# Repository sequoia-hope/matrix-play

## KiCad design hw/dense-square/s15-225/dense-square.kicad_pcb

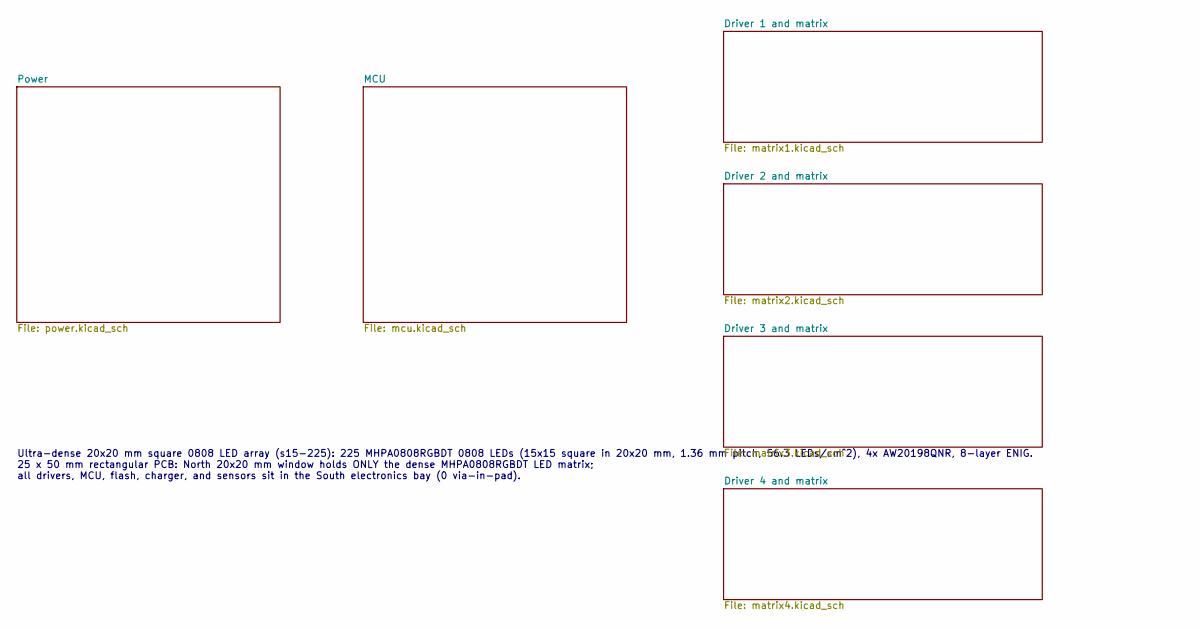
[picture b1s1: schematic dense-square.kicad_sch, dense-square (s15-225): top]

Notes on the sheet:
Ultra-dense 20x20 mm square 0808 LED array (s15-225): 225 MHPA0808RGBDT 0808 LEDs (15x15 square in 20x20 mm, 1.36 mm pitch, 56.3 LEDs/cm^2), 4x AW20198QNR, 8-layer ENIG. 25 x 50 mm rectangular PCB: North 20x20 mm window holds ONLY the dense MHPA0808RGBDT LED matrix; all drivers, MCU, flash, charger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

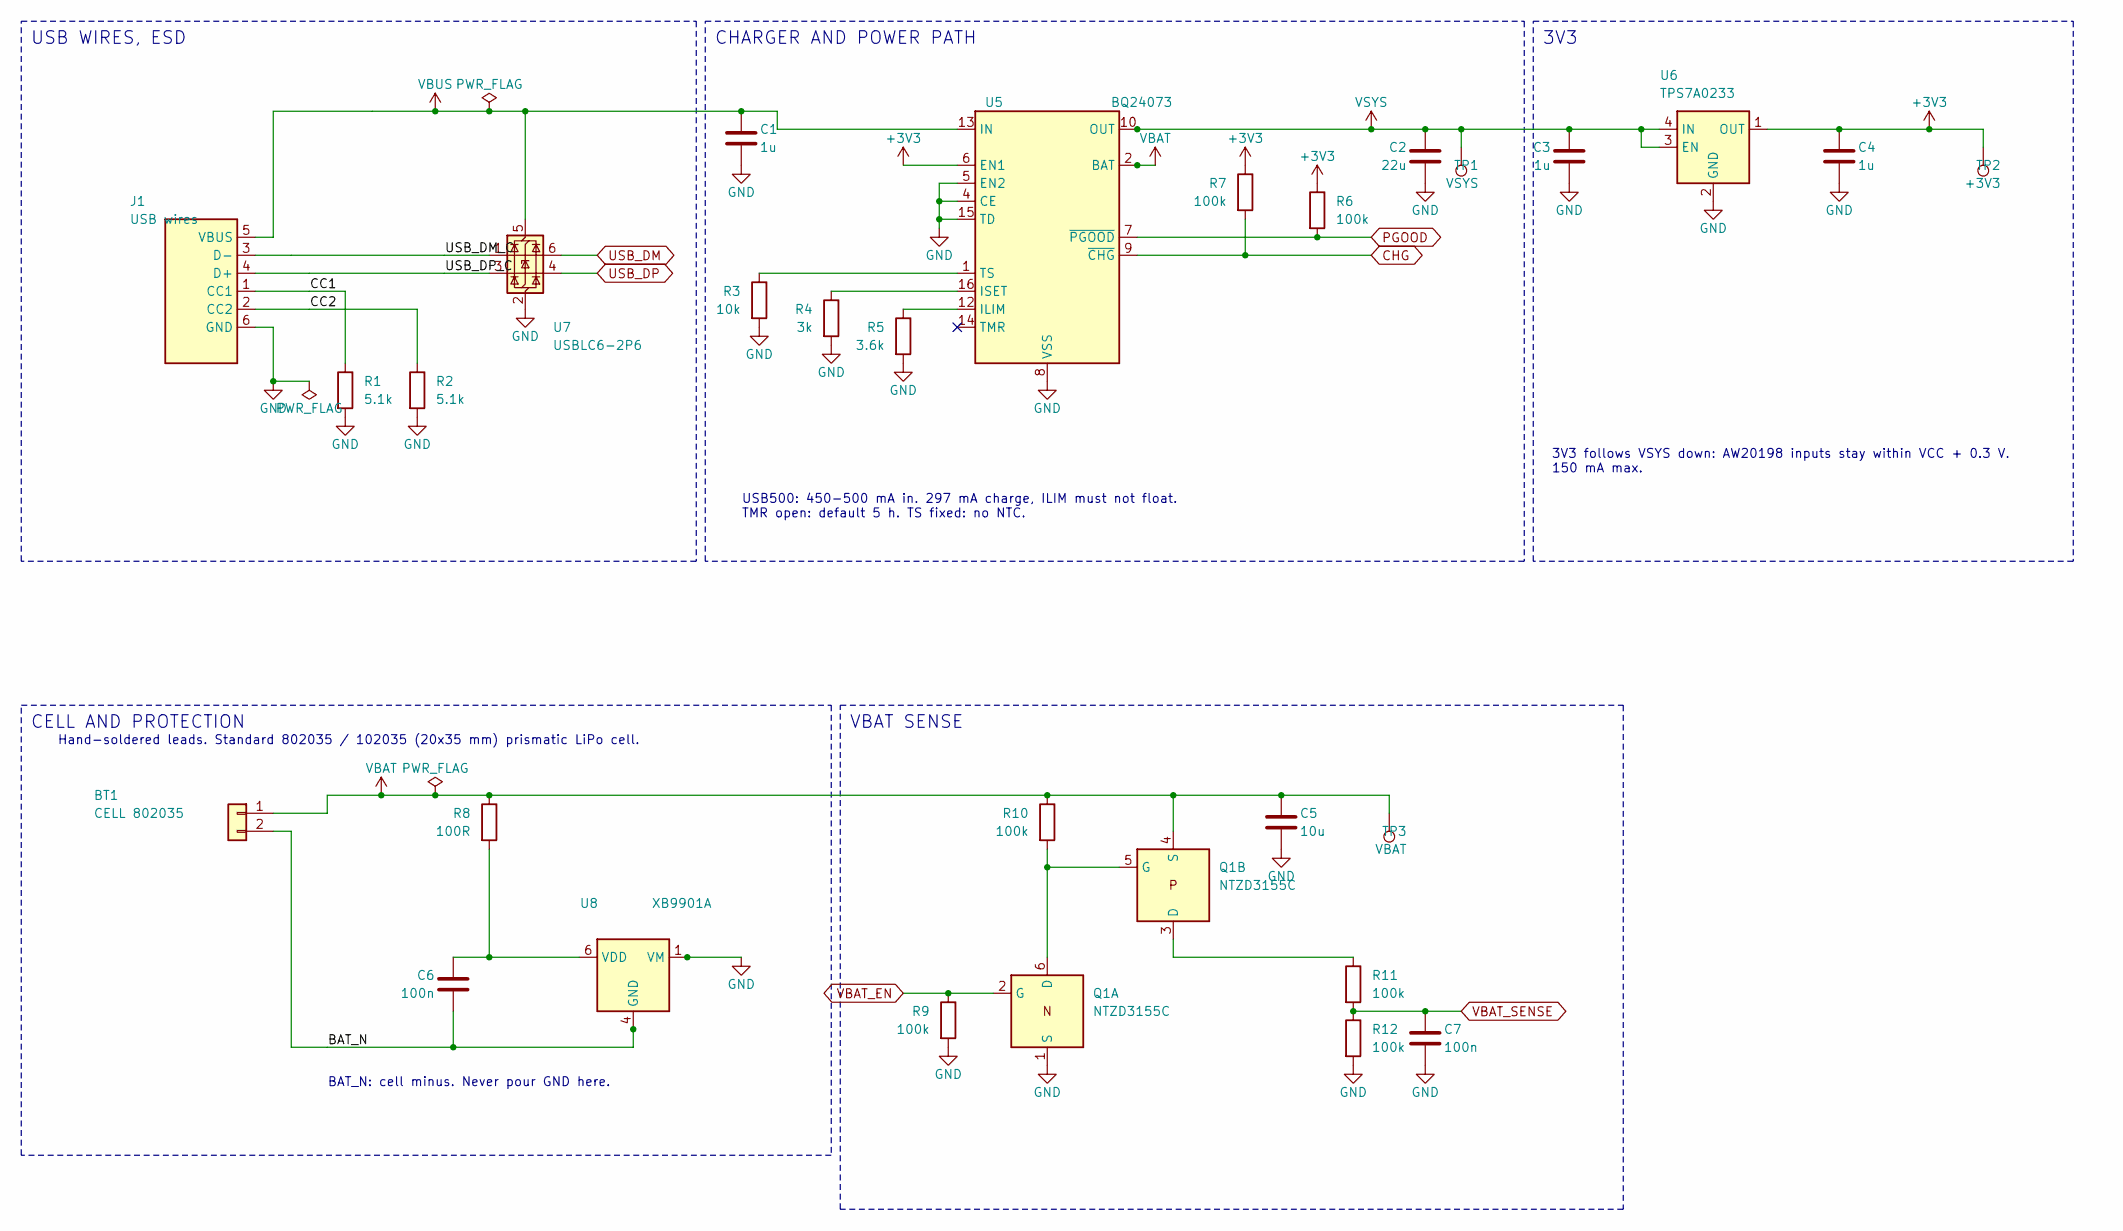
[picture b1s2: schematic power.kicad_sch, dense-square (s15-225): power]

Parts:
BT1: CELL 802035; BatteryPads; MPN 802035
C1, C3, C4: 1u; C_0402_1005Metric; MPN CL05A105KA5NQNC; LCSC C52923
C2: 22u; C_0603_1608Metric; MPN CL10A226MP8NUNE; LCSC C86295
C5: 10u; C_0603_1608Metric; MPN CL10A106KP8NNNC; LCSC C19702
C6, C7: 100n; C_0402_1005Metric; MPN CL05B104KO5NNNC; LCSC C1525
J1: USB wires; USB_Pads; MPN none, wire pads
Q1: NTZD3155C; SOT-563; MPN NTZD3155CT1G; LCSC C236117
R1, R2: 5.1k; R_0402_1005Metric; MPN 0402WGF5101TCE; LCSC C25905
R3: 10k; R_0402_1005Metric; MPN 0402WGF1002TCE; LCSC C25744
R4: 3k; R_0402_1005Metric; MPN 0402WGF3001TCE; LCSC C25784
R5: 3.6k; R_0402_1005Metric; MPN 0402WGF3601TCE; LCSC C25891
R6, R7, R9, R10, R11, R12: 100k; R_0402_1005Metric; MPN 0402WGF1003TCE; LCSC C25741
R8: 100R; R_0402_1005Metric; MPN 0402WGF1000TCE; LCSC C25076
TP1: VSYS; TestPoint_Pad_D1.0mm
TP2: +3V3; TestPoint_Pad_D1.0mm
TP3: VBAT; TestPoint_Pad_D1.0mm
U5: BQ24073; QFN-16-1EP_3x3mm_P0.5mm_EP1.7x1.7mm; MPN BQ24073RGTR; LCSC C15220
U6: TPS7A0233; Texas_X2SON-4_1x1mm_P0.65mm; MPN TPS7A0233PDQNR; LCSC C2860046
U7: USBLC6-2P6; SOT-666; MPN USBLC6-2P6; LCSC C15999
U8: XB9901A; XySemi_DFN-6_1.8x1.4mm; MPN XB9901A; LCSC C669687

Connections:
+3V3: C4.1, R6.1, R7.1, TP2.1, U5.6 (EN1), U6.1 (OUT); also elsewhere on the board
/Power/BAT_N: BT1.2, C6.2, U8.4 (GND), U8.5 (GND)
/Power/CC1: J1.1 (CC1), R1.1
/Power/CC2: J1.2 (CC2), R2.1
/Power/USB_DM_C: J1.3 (D-), U7.1 (I/O1)
/Power/USB_DP_C: J1.4 (D+), U7.3 (I/O2)
CHG: R7.2, U5.9 (~CHG); also elsewhere on the board
unnamed: Q1.5 (G), Q1.6 (D), R10.2
unnamed: Q1.3 (D), R11.1
unnamed: R5.1, U5.12 (ILIM)
unnamed: R4.1, U5.16 (ISET)
unnamed: R3.1, U5.1 (TS)
unnamed: C6.1, R8.2, U8.6 (VDD)
PGOOD: R6.2, U5.7 (~PGOOD); also elsewhere on the board
USB_DM: U7.6 (I/O1); also elsewhere on the board
USB_DP: U7.4 (I/O2); also elsewhere on the board
VBAT_EN: Q1.2 (G), R9.1; also elsewhere on the board
VBAT_SENSE: C7.1, R11.2, R12.1; also elsewhere on the board
VSYS: C2.1, C3.1, TP1.1, U5.10 (OUT), U5.11 (OUT), U6.3 (EN), U6.4 (IN); also elsewhere on the board

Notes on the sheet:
USB WIRES, ESD
USB500: 450-500 mA in. 297 mA charge, ILIM must not float. TMR open: default 5 h. TS fixed: no NTC.
CHARGER AND POWER PATH
3V3 follows VSYS down: AW20198 inputs stay within VCC + 0.3 V. 150 mA max.
3V3
Hand-soldered leads. Standard 802035 / 102035 (20x35 mm) prismatic LiPo cell.
BAT_N: cell minus. Never pour GND here.
CELL AND PROTECTION
VBAT SENSE

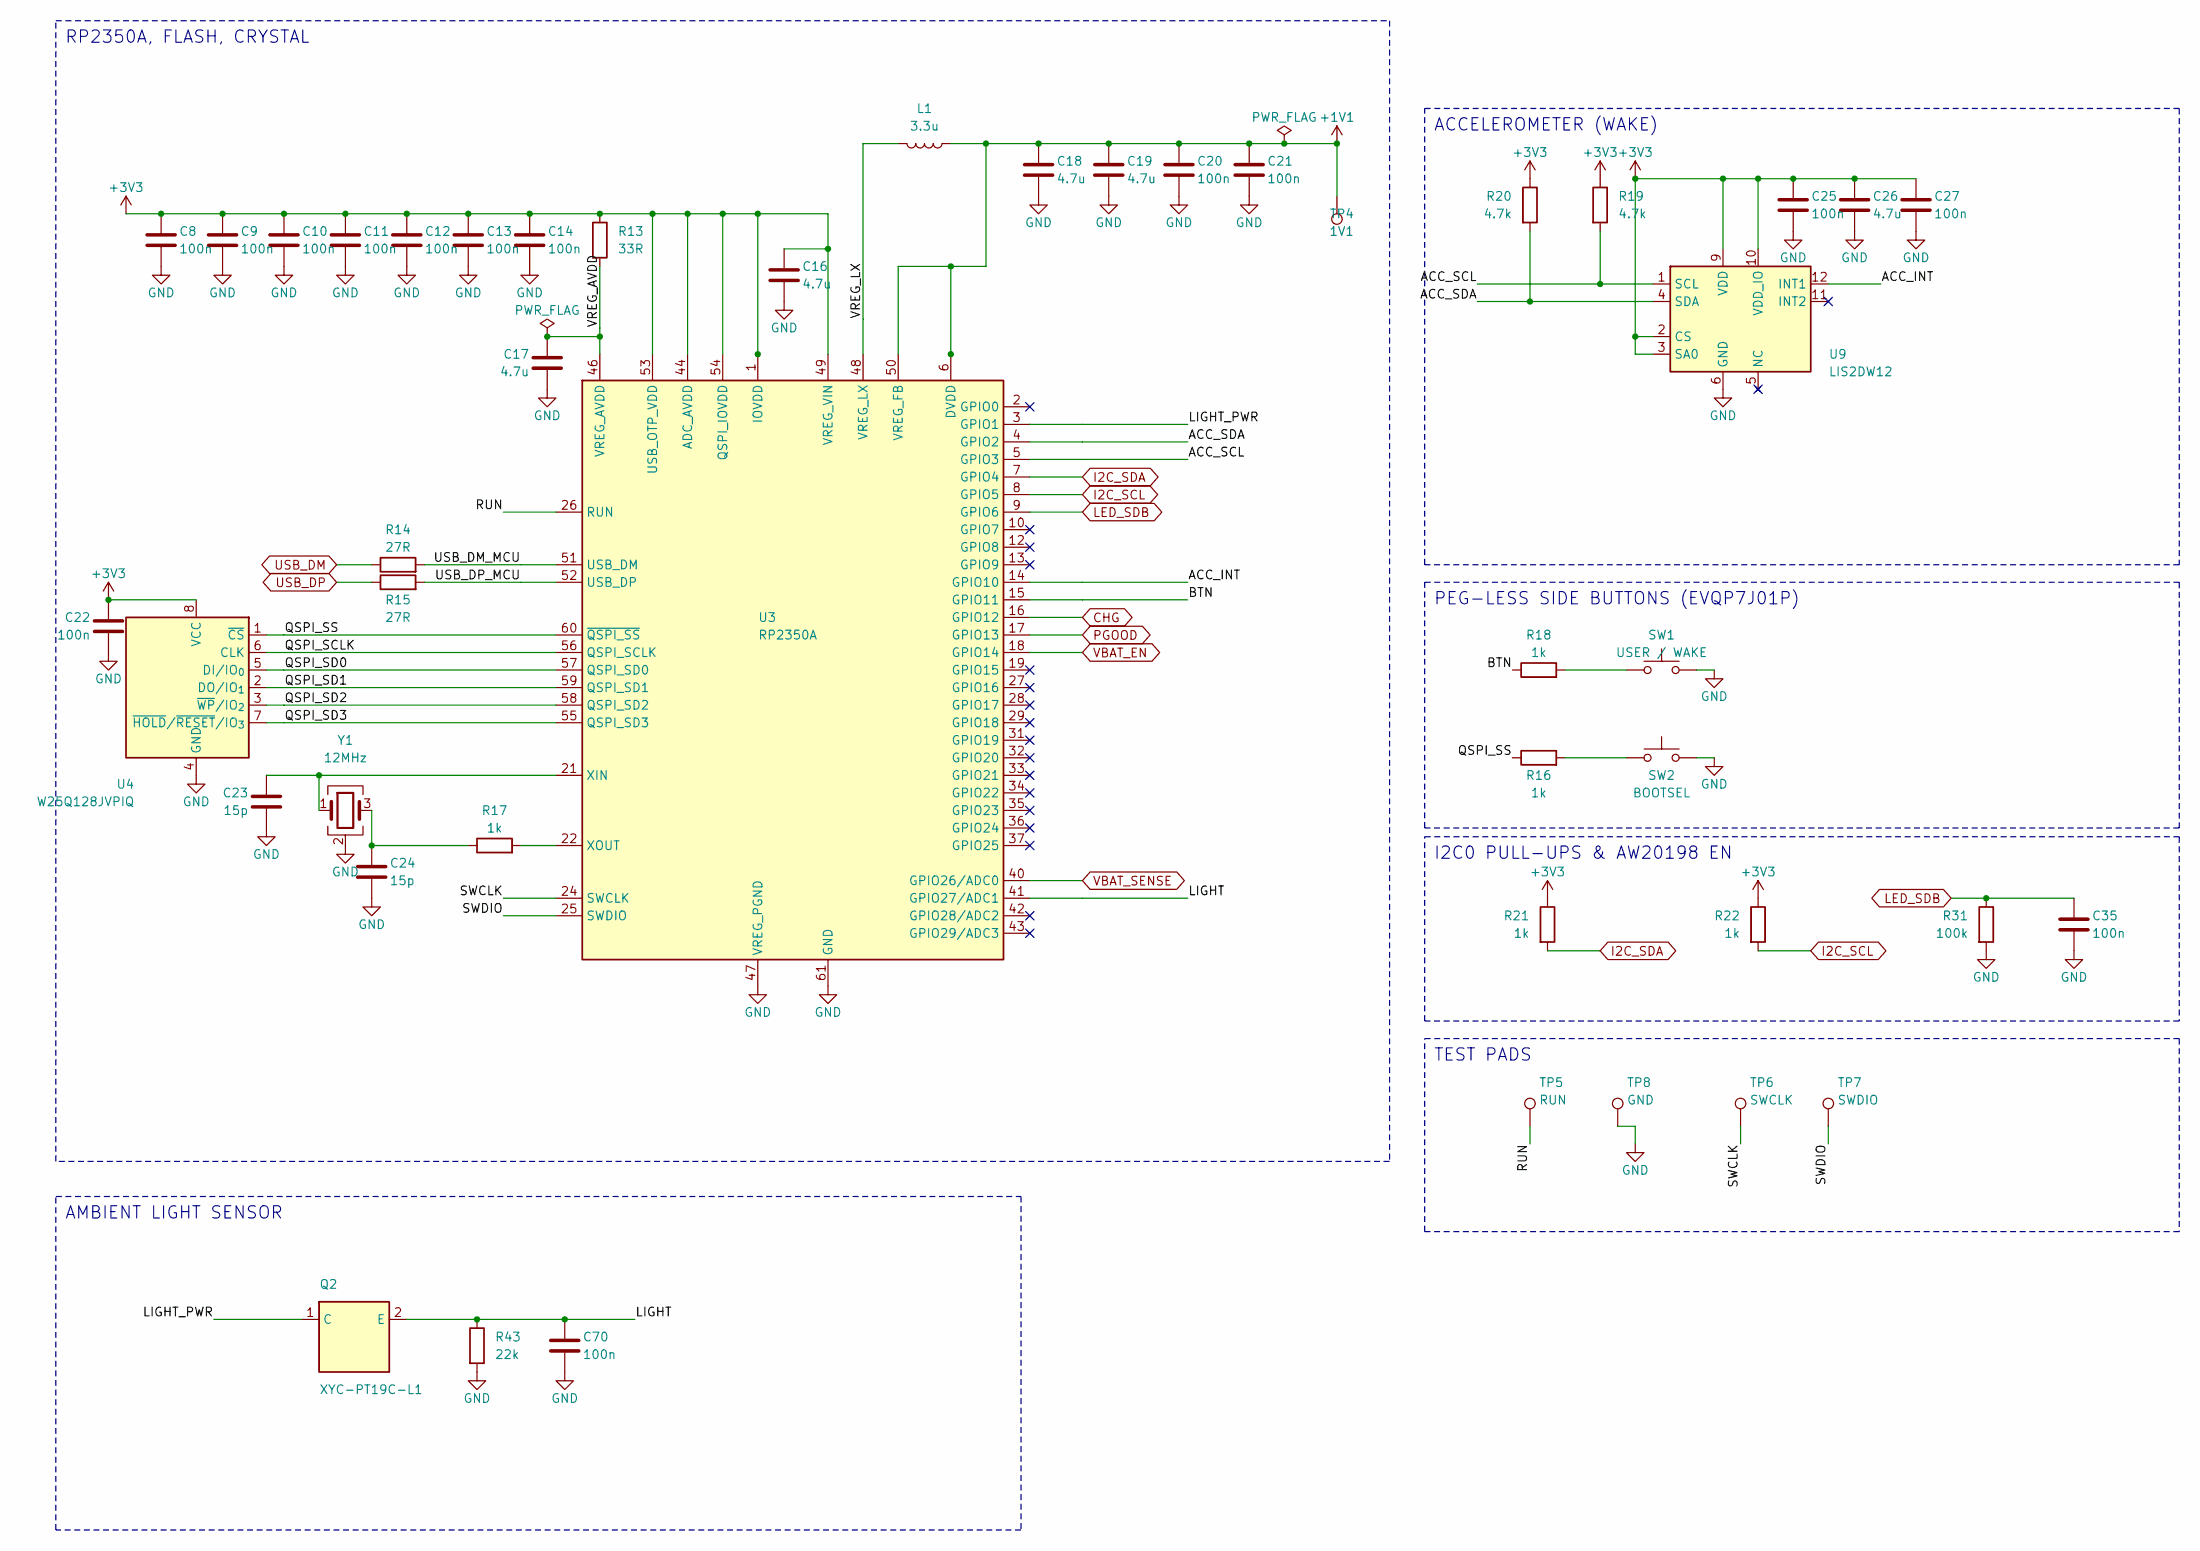
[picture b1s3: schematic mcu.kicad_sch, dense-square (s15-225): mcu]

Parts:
C8, C9, C10, C11, C12, C13, C14, C20, C21, C22, C25, C27, C35, C70: 100n; C_0402_1005Metric; MPN CL05B104KO5NNNC; LCSC C1525
C16, C18: 4.7u; C_0402_1005Metric_small_pads; MPN CL05A475MP5NRNC; LCSC C23733
C17, C19, C26: 4.7u; C_0402_1005Metric; MPN CL05A475MP5NRNC; LCSC C23733
C23, C24: 15p; C_0402_1005Metric; MPN 0402CG150J500NT; LCSC C1548
L1: 3.3u; L_pol_2016; MPN AOTA-B201610S3R3-101-T; LCSC C42411119
Q2: XYC-PT19C-L1; SENSOR_ALS-PT19; MPN XYC-PT19C-L1; LCSC C2693594
R13: 33R; R_0402_1005Metric; MPN 0402WGF330JTCE; LCSC C25105
R14, R15: 27R; R_0402_1005Metric; MPN 0402WGF270JTCE; LCSC C25100
R16, R17, R18, R21, R22: 1k; R_0402_1005Metric; MPN 0402WGF1001TCE; LCSC C11702
R19, R20: 4.7k; R_0402_1005Metric; MPN 0402WGF4701TCE; LCSC C25900
R31: 100k; R_0402_1005Metric; MPN 0402WGF1003TCE; LCSC C25741
R43: 22k; R_0402_1005Metric; MPN 0402WGF2202TCE; LCSC C25768
SW1: USER / WAKE; SW_Panasonic_EVQP7J; MPN EVQP7J01P; LCSC C2828254
SW2: BOOTSEL; SW_Panasonic_EVQP7J; MPN EVQP7J01P; LCSC C2828254
TP4: 1V1; TestPoint_Pad_D1.0mm
TP5: RUN; TestPoint_Pad_D1.0mm
TP6: SWCLK; TestPoint_Pad_D1.0mm
TP7: SWDIO; TestPoint_Pad_D1.0mm
TP8: GND; TestPoint_Pad_D1.0mm
U3: RP2350A; RP2350-QFN-60-1EP_7x7_P0.4mm_EP3.4x3.4mm_ThermalVias; MPN RP2350A; LCSC C42411118
U4: W25Q128JVPIQ; WSON-8_6x5mm_P1.27mm_NoEPCopper; MPN W25Q128JVPIQ; LCSC C190862
U9: LIS2DW12; LGA-12_2x2mm_P0.5mm; MPN LIS2DW12TR; LCSC C189624
Y1: 12MHz; Crystal_SMD_3225-4Pin_3.2x2.5mm; MPN ABM8-272-T3; LCSC C20625731

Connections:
+3V3: C8.1, C9.1, C10.1, C11.1, C12.1, C13.1, C14.1, C16.1, C22.1, C25.1, C26.1, C27.1, R13.1, R19.1, R20.1, R21.1, R22.1, U3.1 (IOVDD), U3.11 (IOVDD), U3.20 (IOVDD), U3.30 (IOVDD), U3.38 (IOVDD), U3.44 (ADC_AVDD), U3.45 (IOVDD), U3.49 (VREG_VIN), U3.53 (USB_OTP_VDD), U3.54 (QSPI_IOVDD), U4.8 (VCC), U9.2 (CS), U9.3 (SA0), U9.9 (VDD), U9.10 (VDD_IO); also elsewhere on the board
/MCU/ACC_INT: U3.14 (GPIO10), U9.12 (INT1)
/MCU/ACC_SCL: R19.2, U3.5 (GPIO3), U9.1 (SCL)
/MCU/ACC_SDA: R20.2, U3.4 (GPIO2), U9.4 (SDA)
/MCU/BTN: R18.1, U3.15 (GPIO11)
/MCU/LIGHT: C70.1, Q2.2 (E), R43.1, U3.41 (GPIO27/ADC1)
/MCU/LIGHT_PWR: Q2.1 (C), U3.3 (GPIO1)
/MCU/QSPI_SCLK: U3.56 (QSPI_SCLK), U4.6 (CLK)
/MCU/QSPI_SD0: U3.57 (QSPI_SD0), U4.5 (DI/IO_{0})
/MCU/QSPI_SD1: U3.59 (QSPI_SD1), U4.2 (DO/IO_{1})
/MCU/QSPI_SD2: U3.58 (QSPI_SD2), U4.3 (~WP/IO_{2})
/MCU/QSPI_SD3: U3.55 (QSPI_SD3), U4.7 (~HOLD/~RESET/IO_{3})
/MCU/QSPI_SS: R16.1, U3.60 (~QSPI_SS), U4.1 (~CS)
/MCU/RUN: TP5.1, U3.26 (RUN)
/MCU/SWCLK: TP6.1, U3.24 (SWCLK)
/MCU/SWDIO: TP7.1, U3.25 (SWDIO)
/MCU/USB_DM_MCU: R14.2, U3.51 (USB_DM)
/MCU/USB_DP_MCU: R15.2, U3.52 (USB_DP)
/MCU/VREG_LX: L1.2, U3.48 (VREG_LX)
CHG: U3.16 (GPIO12); also elsewhere on the board
I2C_SCL: R22.2, U3.8 (GPIO5); also elsewhere on the board
I2C_SDA: R21.2, U3.7 (GPIO4); also elsewhere on the board
LED_SDB: C35.1, R31.1, U3.9 (GPIO6); also elsewhere on the board
unnamed: C24.1, R17.1, Y1.3
unnamed: R16.2, SW2.1
unnamed: R18.2, SW1.1
unnamed: C23.1, U3.21 (XIN), Y1.1
unnamed: R17.2, U3.22 (XOUT)
PGOOD: U3.17 (GPIO13); also elsewhere on the board
USB_DM: R14.1; also elsewhere on the board
USB_DP: R15.1; also elsewhere on the board
VBAT_EN: U3.18 (GPIO14); also elsewhere on the board
VBAT_SENSE: U3.40 (GPIO26/ADC0); also elsewhere on the board

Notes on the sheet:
RP2350A, FLASH, CRYSTAL
ACCELEROMETER (WAKE)
PEG-LESS SIDE BUTTONS (EVQP7J01P)
I2C0 PULL-UPS & AW20198 EN
TEST PADS
AMBIENT LIGHT SENSOR

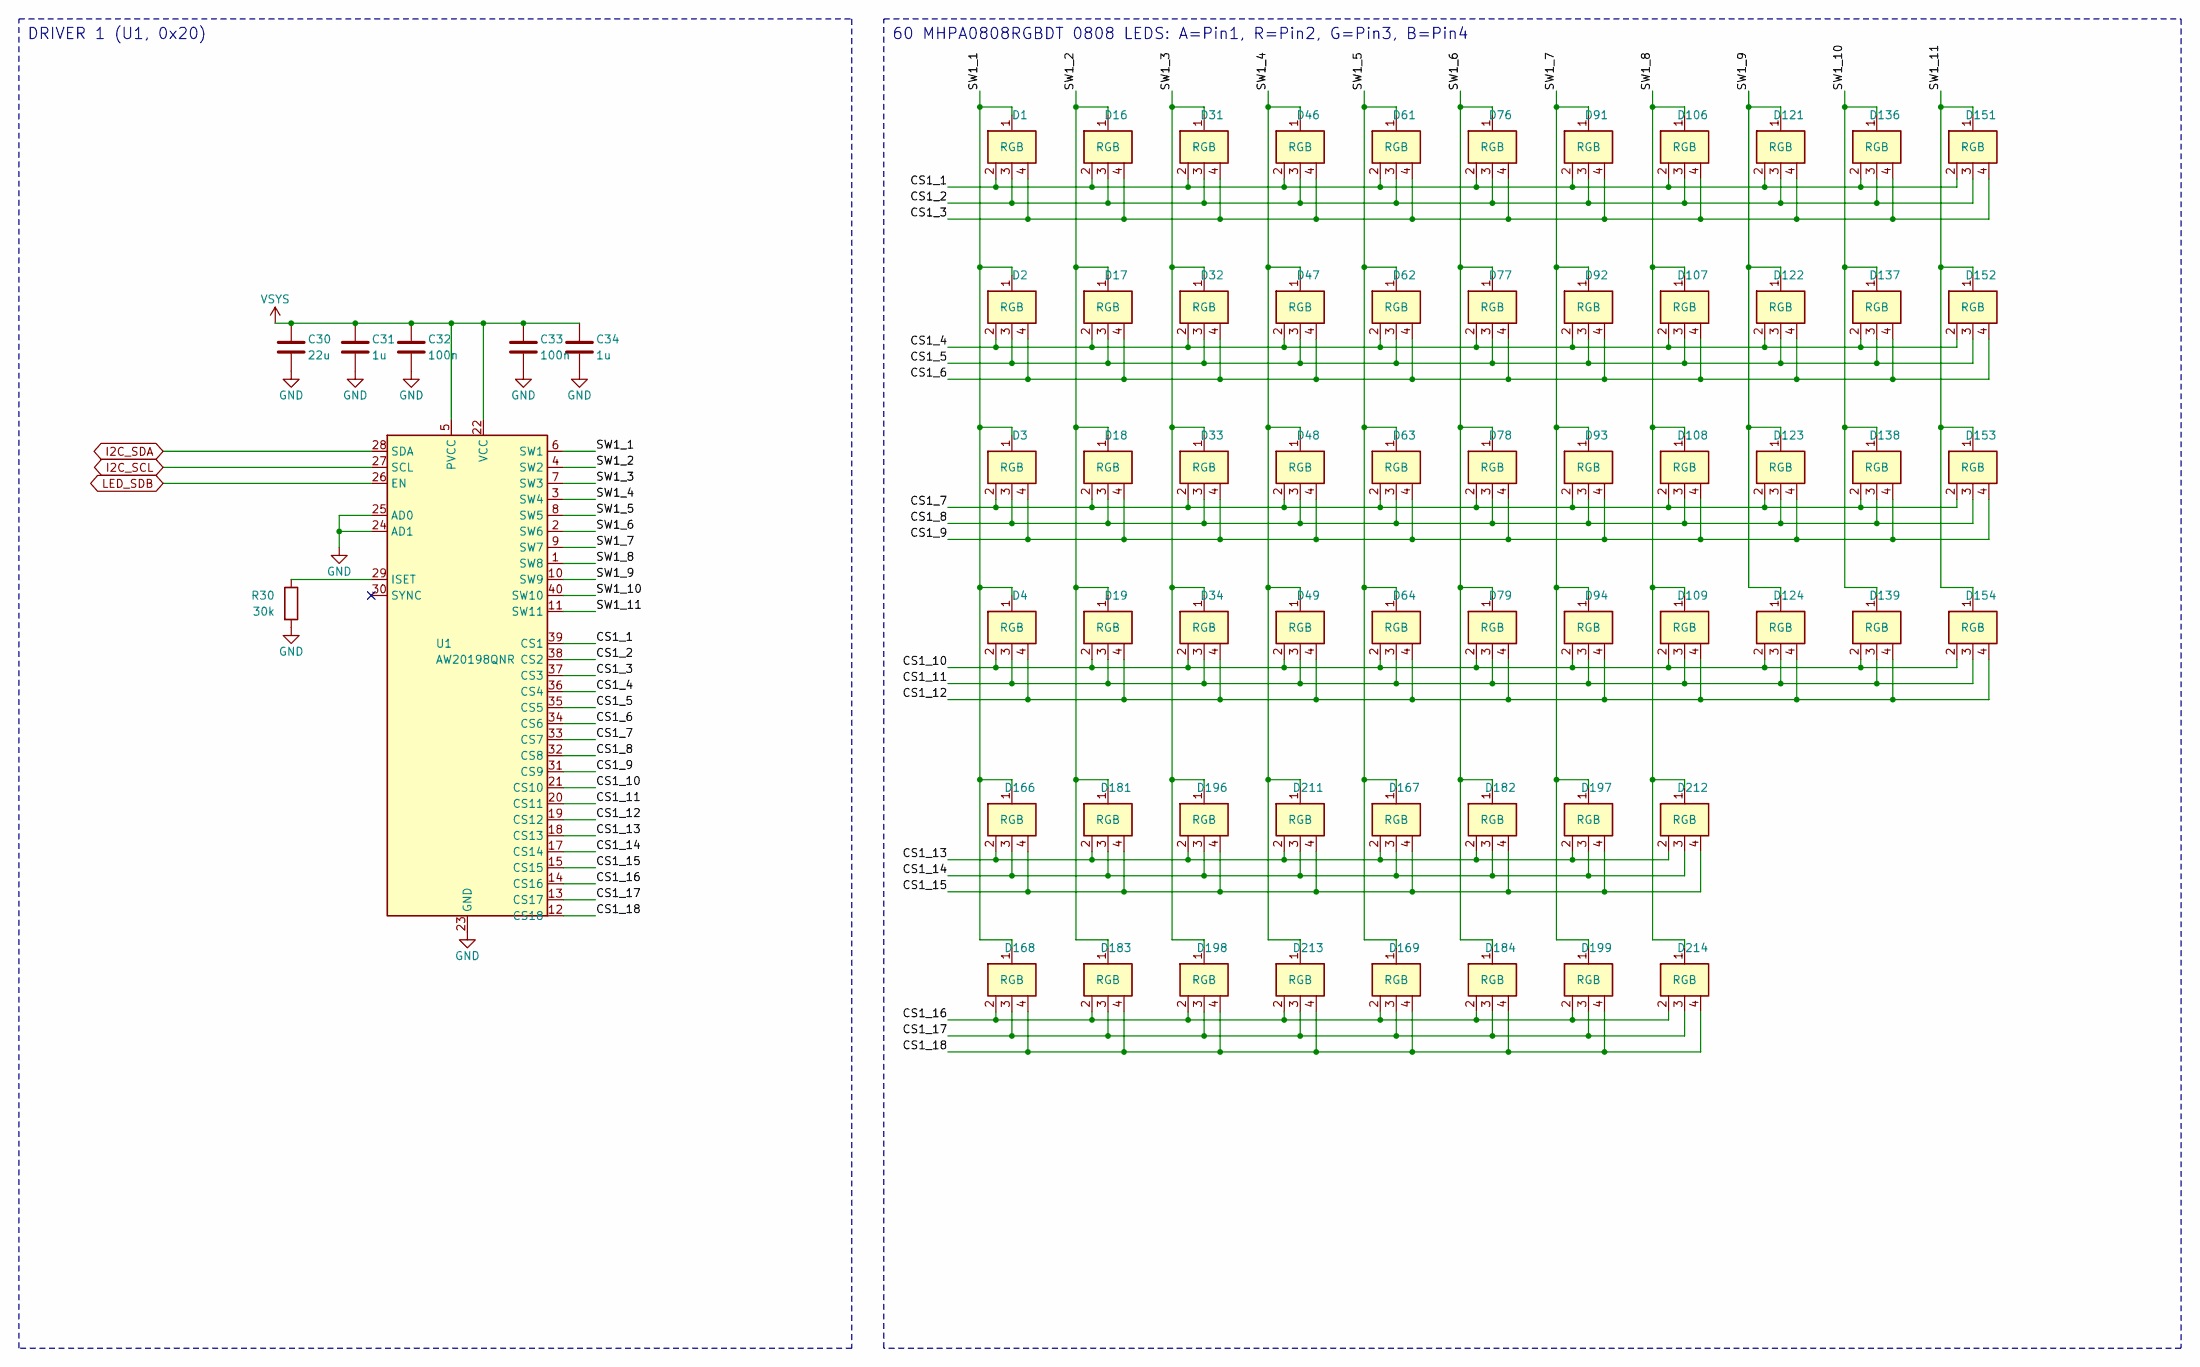
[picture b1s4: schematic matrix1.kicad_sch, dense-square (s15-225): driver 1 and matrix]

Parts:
C30: 22u; C_0603_1608Metric; MPN CL10A226MP8NUNE; LCSC C86295
C31, C34: 1u; C_0402_1005Metric; MPN CL05A105KA5NQNC; LCSC C52923
C32, C33: 100n; C_0402_1005Metric; MPN CL05B104KO5NNNC; LCSC C1525
D1, D2, D3, D4, D16, D17, D18, D19, D31, D32, D33, D34, D46, D47, D48, D49, D61, D62, D63, D64, D76, D77, D78, D79, D91, D92, D93, D94, D106, D107, D108, D109, D121, D122, D123, D124, D136, D137, D138, D139, D151, D152, D153, D154, D166, D167, D168, D169, D181, D182, D183, D184, D196, D197, D198, D199, D211, D212, D213, D214: RGB; LED_MHPA0808RGBDT; MPN MHPA0808RGBDT; LCSC C404279
R30: 30k; R_0402_1005Metric; MPN 0402WGF3002TCE; LCSC C25776
U1: AW20198QNR; AW20198_QFN-40-1EP_5x5mm_P0.4mm_EP3.4x3.4mm; MPN AW20198QNR; LCSC C5137654

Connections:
/Driver 1 and matrix/CS1_1: D1.2 (R), D16.2 (R), D31.2 (R), D46.2 (R), D61.2 (R), D76.2 (R), D91.2 (R), D106.2 (R), D121.2 (R), D136.2 (R), D151.2 (R), U1.39 (CS1)
/Driver 1 and matrix/CS1_2: D1.3 (G), D16.3 (G), D31.3 (G), D46.3 (G), D61.3 (G), D76.3 (G), D91.3 (G), D106.3 (G), D121.3 (G), D136.3 (G), D151.3 (G), U1.38 (CS2)
/Driver 1 and matrix/CS1_3: D1.4 (B), D16.4 (B), D31.4 (B), D46.4 (B), D61.4 (B), D76.4 (B), D91.4 (B), D106.4 (B), D121.4 (B), D136.4 (B), D151.4 (B), U1.37 (CS3)
/Driver 1 and matrix/CS1_4: D2.2 (R), D17.2 (R), D32.2 (R), D47.2 (R), D62.2 (R), D77.2 (R), D92.2 (R), D107.2 (R), D122.2 (R), D137.2 (R), D152.2 (R), U1.36 (CS4)
/Driver 1 and matrix/CS1_5: D2.3 (G), D17.3 (G), D32.3 (G), D47.3 (G), D62.3 (G), D77.3 (G), D92.3 (G), D107.3 (G), D122.3 (G), D137.3 (G), D152.3 (G), U1.35 (CS5)
/Driver 1 and matrix/CS1_6: D2.4 (B), D17.4 (B), D32.4 (B), D47.4 (B), D62.4 (B), D77.4 (B), D92.4 (B), D107.4 (B), D122.4 (B), D137.4 (B), D152.4 (B), U1.34 (CS6)
/Driver 1 and matrix/CS1_7: D3.2 (R), D18.2 (R), D33.2 (R), D48.2 (R), D63.2 (R), D78.2 (R), D93.2 (R), D108.2 (R), D123.2 (R), D138.2 (R), D153.2 (R), U1.33 (CS7)
/Driver 1 and matrix/CS1_8: D3.3 (G), D18.3 (G), D33.3 (G), D48.3 (G), D63.3 (G), D78.3 (G), D93.3 (G), D108.3 (G), D123.3 (G), D138.3 (G), D153.3 (G), U1.32 (CS8)
/Driver 1 and matrix/CS1_9: D3.4 (B), D18.4 (B), D33.4 (B), D48.4 (B), D63.4 (B), D78.4 (B), D93.4 (B), D108.4 (B), D123.4 (B), D138.4 (B), D153.4 (B), U1.31 (CS9)
/Driver 1 and matrix/CS1_10: D4.2 (R), D19.2 (R), D34.2 (R), D49.2 (R), D64.2 (R), D79.2 (R), D94.2 (R), D109.2 (R), D124.2 (R), D139.2 (R), D154.2 (R), U1.21 (CS10)
/Driver 1 and matrix/CS1_11: D4.3 (G), D19.3 (G), D34.3 (G), D49.3 (G), D64.3 (G), D79.3 (G), D94.3 (G), D109.3 (G), D124.3 (G), D139.3 (G), D154.3 (G), U1.20 (CS11)
/Driver 1 and matrix/CS1_12: D4.4 (B), D19.4 (B), D34.4 (B), D49.4 (B), D64.4 (B), D79.4 (B), D94.4 (B), D109.4 (B), D124.4 (B), D139.4 (B), D154.4 (B), U1.19 (CS12)
/Driver 1 and matrix/CS1_13: D166.2 (R), D167.2 (R), D181.2 (R), D182.2 (R), D196.2 (R), D197.2 (R), D211.2 (R), D212.2 (R), U1.18 (CS13)
/Driver 1 and matrix/CS1_14: D166.3 (G), D167.3 (G), D181.3 (G), D182.3 (G), D196.3 (G), D197.3 (G), D211.3 (G), D212.3 (G), U1.17 (CS14)
/Driver 1 and matrix/CS1_15: D166.4 (B), D167.4 (B), D181.4 (B), D182.4 (B), D196.4 (B), D197.4 (B), D211.4 (B), D212.4 (B), U1.15 (CS15)
/Driver 1 and matrix/CS1_16: D168.2 (R), D169.2 (R), D183.2 (R), D184.2 (R), D198.2 (R), D199.2 (R), D213.2 (R), D214.2 (R), U1.14 (CS16)
/Driver 1 and matrix/CS1_17: D168.3 (G), D169.3 (G), D183.3 (G), D184.3 (G), D198.3 (G), D199.3 (G), D213.3 (G), D214.3 (G), U1.13 (CS17)
/Driver 1 and matrix/CS1_18: D168.4 (B), D169.4 (B), D183.4 (B), D184.4 (B), D198.4 (B), D199.4 (B), D213.4 (B), D214.4 (B), U1.12 (CS18)
/Driver 1 and matrix/SW1_1: D1.1 (A), D2.1 (A), D3.1 (A), D4.1 (A), D166.1 (A), D168.1 (A), U1.6 (SW1)
/Driver 1 and matrix/SW1_2: D16.1 (A), D17.1 (A), D18.1 (A), D19.1 (A), D181.1 (A), D183.1 (A), U1.4 (SW2)
/Driver 1 and matrix/SW1_3: D31.1 (A), D32.1 (A), D33.1 (A), D34.1 (A), D196.1 (A), D198.1 (A), U1.7 (SW3)
/Driver 1 and matrix/SW1_4: D46.1 (A), D47.1 (A), D48.1 (A), D49.1 (A), D211.1 (A), D213.1 (A), U1.3 (SW4)
/Driver 1 and matrix/SW1_5: D61.1 (A), D62.1 (A), D63.1 (A), D64.1 (A), D167.1 (A), D169.1 (A), U1.8 (SW5)
/Driver 1 and matrix/SW1_6: D76.1 (A), D77.1 (A), D78.1 (A), D79.1 (A), D182.1 (A), D184.1 (A), U1.2 (SW6)
/Driver 1 and matrix/SW1_7: D91.1 (A), D92.1 (A), D93.1 (A), D94.1 (A), D197.1 (A), D199.1 (A), U1.9 (SW7)
/Driver 1 and matrix/SW1_8: D106.1 (A), D107.1 (A), D108.1 (A), D109.1 (A), D212.1 (A), D214.1 (A), U1.1 (SW8)
/Driver 1 and matrix/SW1_9: D121.1 (A), D122.1 (A), D123.1 (A), D124.1 (A), U1.10 (SW9)
/Driver 1 and matrix/SW1_10: D136.1 (A), D137.1 (A), D138.1 (A), D139.1 (A), U1.40 (SW10)
/Driver 1 and matrix/SW1_11: D151.1 (A), D152.1 (A), D153.1 (A), D154.1 (A), U1.11 (SW11)
I2C_SCL: U1.27 (SCL); also elsewhere on the board
I2C_SDA: U1.28 (SDA); also elsewhere on the board
LED_SDB: U1.26 (EN); also elsewhere on the board
unnamed: R30.1, U1.29 (ISET)
VSYS: C30.1, C31.1, C32.1, C33.1, C34.1, U1.5 (PVCC), U1.22 (VCC); also elsewhere on the board

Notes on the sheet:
DRIVER 1 (U1, 0x20)
60 MHPA0808RGBDT 0808 LEDS: A=Pin1, R=Pin2, G=Pin3, B=Pin4

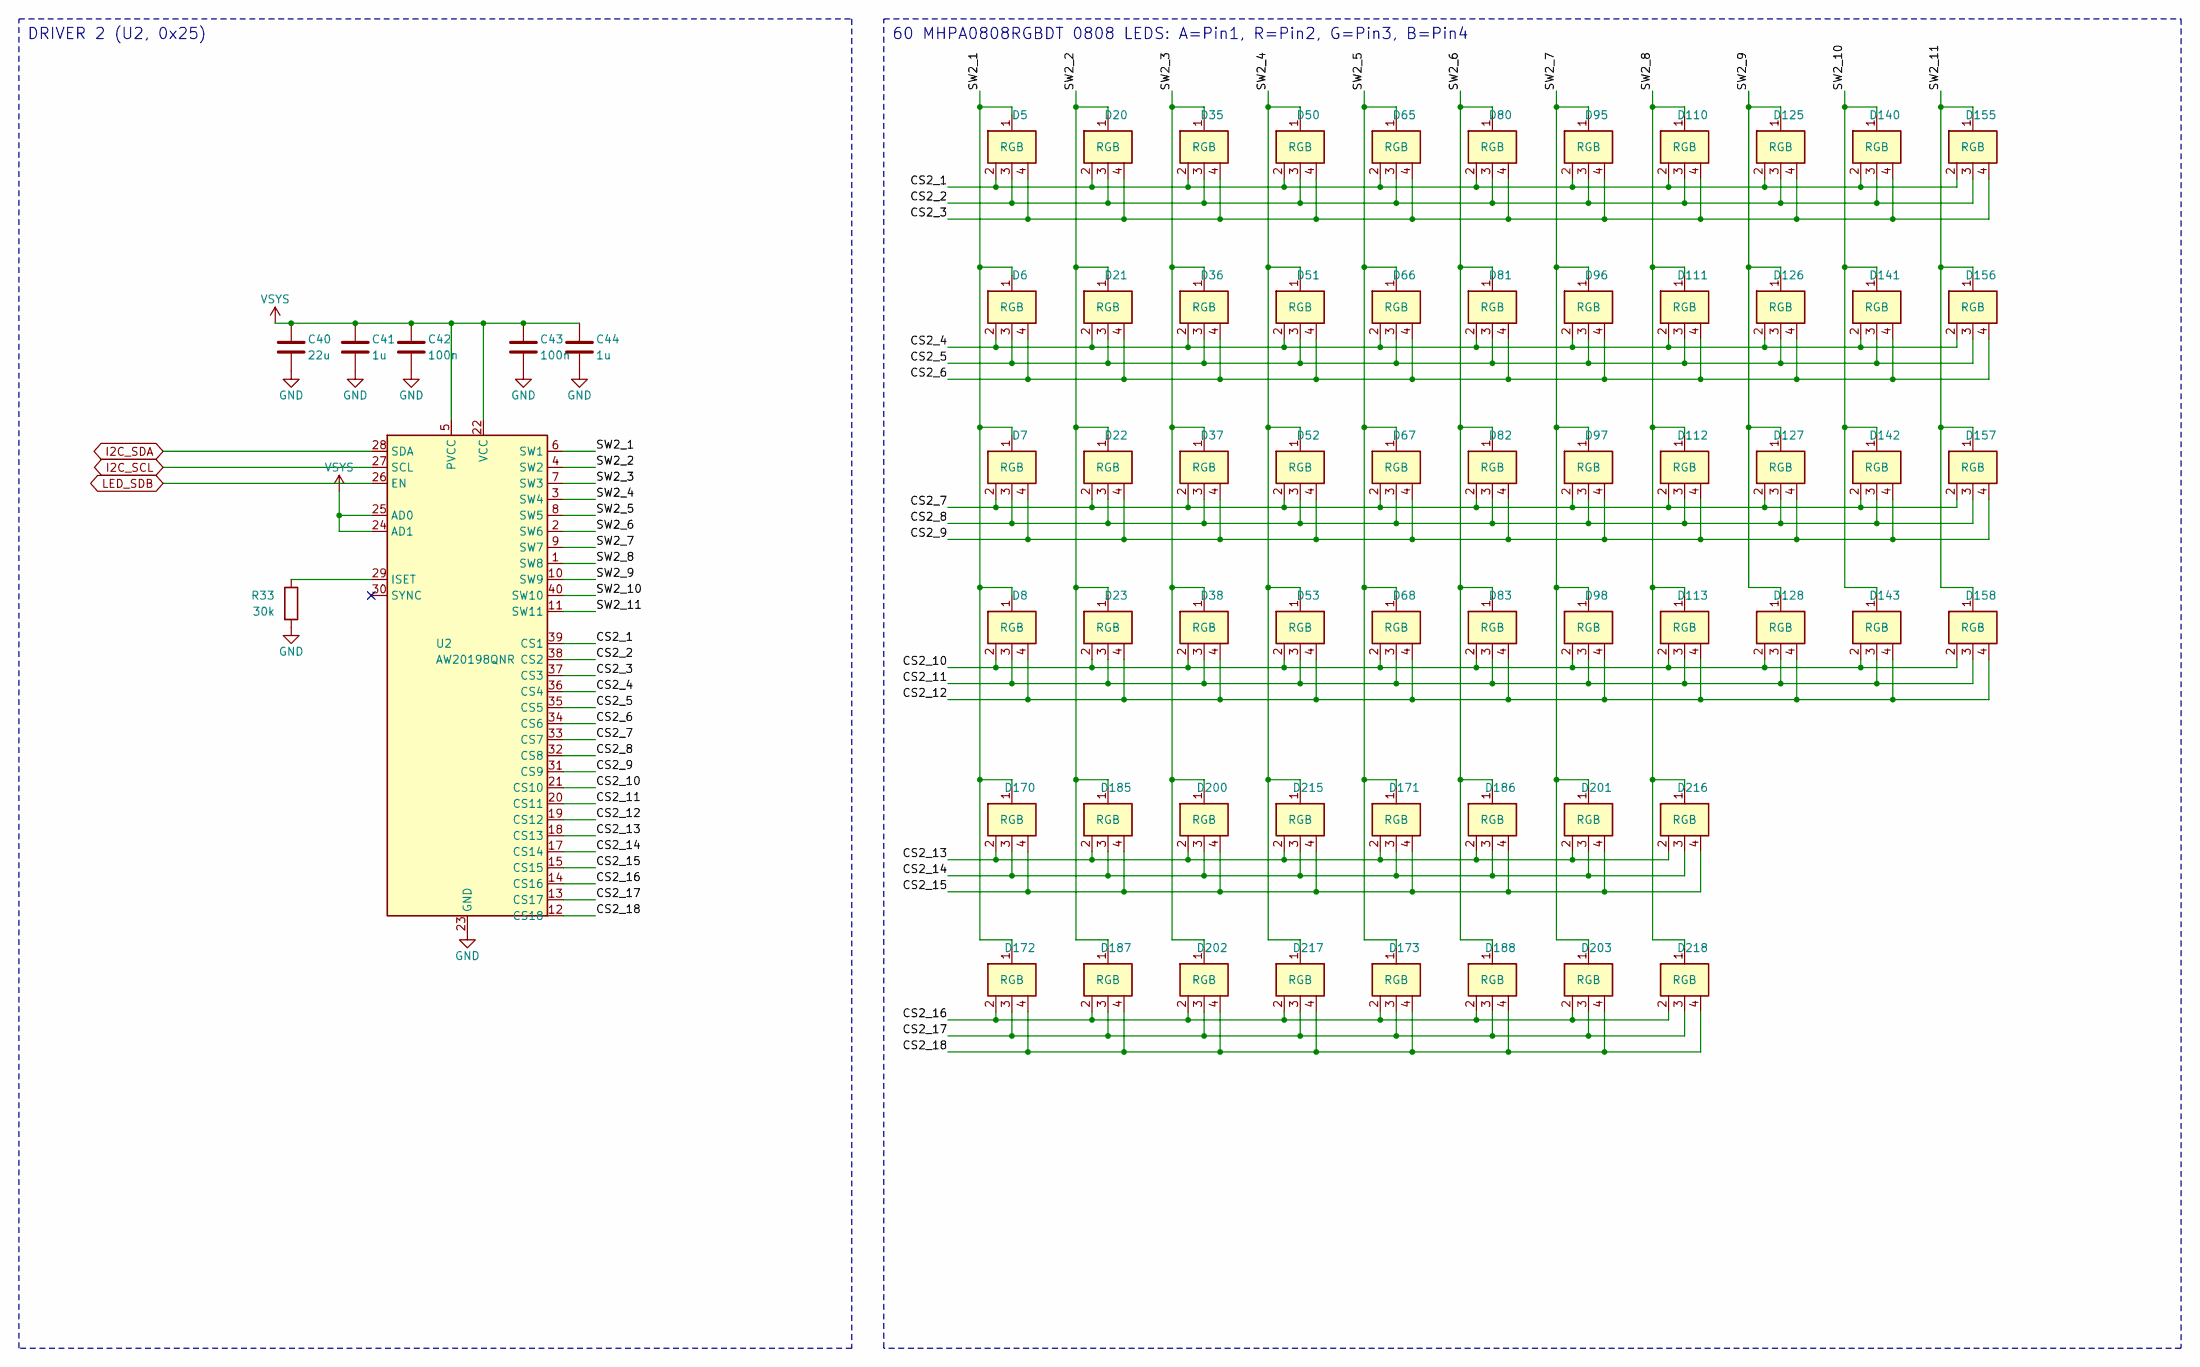
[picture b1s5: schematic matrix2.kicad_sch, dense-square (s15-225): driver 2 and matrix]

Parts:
C40: 22u; C_0603_1608Metric; MPN CL10A226MP8NUNE; LCSC C86295
C41, C44: 1u; C_0402_1005Metric; MPN CL05A105KA5NQNC; LCSC C52923
C42, C43: 100n; C_0402_1005Metric; MPN CL05B104KO5NNNC; LCSC C1525
D5, D6, D7, D8, D20, D21, D22, D23, D35, D36, D37, D38, D50, D51, D52, D53, D65, D66, D67, D68, D80, D81, D82, D83, D95, D96, D97, D98, D110, D111, D112, D113, D125, D126, D127, D128, D140, D141, D142, D143, D155, D156, D157, D158, D170, D171, D172, D173, D185, D186, D187, D188, D200, D201, D202, D203, D215, D216, D217, D218: RGB; LED_MHPA0808RGBDT; MPN MHPA0808RGBDT; LCSC C404279
R33: 30k; R_0402_1005Metric; MPN 0402WGF3002TCE; LCSC C25776
U2: AW20198QNR; AW20198_QFN-40-1EP_5x5mm_P0.4mm_EP3.4x3.4mm; MPN AW20198QNR; LCSC C5137654

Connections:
/Driver 2 and matrix/CS2_1: D5.2 (R), D20.2 (R), D35.2 (R), D50.2 (R), D65.2 (R), D80.2 (R), D95.2 (R), D110.2 (R), D125.2 (R), D140.2 (R), D155.2 (R), U2.39 (CS1)
/Driver 2 and matrix/CS2_2: D5.3 (G), D20.3 (G), D35.3 (G), D50.3 (G), D65.3 (G), D80.3 (G), D95.3 (G), D110.3 (G), D125.3 (G), D140.3 (G), D155.3 (G), U2.38 (CS2)
/Driver 2 and matrix/CS2_3: D5.4 (B), D20.4 (B), D35.4 (B), D50.4 (B), D65.4 (B), D80.4 (B), D95.4 (B), D110.4 (B), D125.4 (B), D140.4 (B), D155.4 (B), U2.37 (CS3)
/Driver 2 and matrix/CS2_4: D6.2 (R), D21.2 (R), D36.2 (R), D51.2 (R), D66.2 (R), D81.2 (R), D96.2 (R), D111.2 (R), D126.2 (R), D141.2 (R), D156.2 (R), U2.36 (CS4)
/Driver 2 and matrix/CS2_5: D6.3 (G), D21.3 (G), D36.3 (G), D51.3 (G), D66.3 (G), D81.3 (G), D96.3 (G), D111.3 (G), D126.3 (G), D141.3 (G), D156.3 (G), U2.35 (CS5)
/Driver 2 and matrix/CS2_6: D6.4 (B), D21.4 (B), D36.4 (B), D51.4 (B), D66.4 (B), D81.4 (B), D96.4 (B), D111.4 (B), D126.4 (B), D141.4 (B), D156.4 (B), U2.34 (CS6)
/Driver 2 and matrix/CS2_7: D7.2 (R), D22.2 (R), D37.2 (R), D52.2 (R), D67.2 (R), D82.2 (R), D97.2 (R), D112.2 (R), D127.2 (R), D142.2 (R), D157.2 (R), U2.33 (CS7)
/Driver 2 and matrix/CS2_8: D7.3 (G), D22.3 (G), D37.3 (G), D52.3 (G), D67.3 (G), D82.3 (G), D97.3 (G), D112.3 (G), D127.3 (G), D142.3 (G), D157.3 (G), U2.32 (CS8)
/Driver 2 and matrix/CS2_9: D7.4 (B), D22.4 (B), D37.4 (B), D52.4 (B), D67.4 (B), D82.4 (B), D97.4 (B), D112.4 (B), D127.4 (B), D142.4 (B), D157.4 (B), U2.31 (CS9)
/Driver 2 and matrix/CS2_10: D8.2 (R), D23.2 (R), D38.2 (R), D53.2 (R), D68.2 (R), D83.2 (R), D98.2 (R), D113.2 (R), D128.2 (R), D143.2 (R), D158.2 (R), U2.21 (CS10)
/Driver 2 and matrix/CS2_11: D8.3 (G), D23.3 (G), D38.3 (G), D53.3 (G), D68.3 (G), D83.3 (G), D98.3 (G), D113.3 (G), D128.3 (G), D143.3 (G), D158.3 (G), U2.20 (CS11)
/Driver 2 and matrix/CS2_12: D8.4 (B), D23.4 (B), D38.4 (B), D53.4 (B), D68.4 (B), D83.4 (B), D98.4 (B), D113.4 (B), D128.4 (B), D143.4 (B), D158.4 (B), U2.19 (CS12)
/Driver 2 and matrix/CS2_13: D170.2 (R), D171.2 (R), D185.2 (R), D186.2 (R), D200.2 (R), D201.2 (R), D215.2 (R), D216.2 (R), U2.18 (CS13)
/Driver 2 and matrix/CS2_14: D170.3 (G), D171.3 (G), D185.3 (G), D186.3 (G), D200.3 (G), D201.3 (G), D215.3 (G), D216.3 (G), U2.17 (CS14)
/Driver 2 and matrix/CS2_15: D170.4 (B), D171.4 (B), D185.4 (B), D186.4 (B), D200.4 (B), D201.4 (B), D215.4 (B), D216.4 (B), U2.15 (CS15)
/Driver 2 and matrix/CS2_16: D172.2 (R), D173.2 (R), D187.2 (R), D188.2 (R), D202.2 (R), D203.2 (R), D217.2 (R), D218.2 (R), U2.14 (CS16)
/Driver 2 and matrix/CS2_17: D172.3 (G), D173.3 (G), D187.3 (G), D188.3 (G), D202.3 (G), D203.3 (G), D217.3 (G), D218.3 (G), U2.13 (CS17)
/Driver 2 and matrix/CS2_18: D172.4 (B), D173.4 (B), D187.4 (B), D188.4 (B), D202.4 (B), D203.4 (B), D217.4 (B), D218.4 (B), U2.12 (CS18)
/Driver 2 and matrix/SW2_1: D5.1 (A), D6.1 (A), D7.1 (A), D8.1 (A), D170.1 (A), D172.1 (A), U2.6 (SW1)
/Driver 2 and matrix/SW2_2: D20.1 (A), D21.1 (A), D22.1 (A), D23.1 (A), D185.1 (A), D187.1 (A), U2.4 (SW2)
/Driver 2 and matrix/SW2_3: D35.1 (A), D36.1 (A), D37.1 (A), D38.1 (A), D200.1 (A), D202.1 (A), U2.7 (SW3)
/Driver 2 and matrix/SW2_4: D50.1 (A), D51.1 (A), D52.1 (A), D53.1 (A), D215.1 (A), D217.1 (A), U2.3 (SW4)
/Driver 2 and matrix/SW2_5: D65.1 (A), D66.1 (A), D67.1 (A), D68.1 (A), D171.1 (A), D173.1 (A), U2.8 (SW5)
/Driver 2 and matrix/SW2_6: D80.1 (A), D81.1 (A), D82.1 (A), D83.1 (A), D186.1 (A), D188.1 (A), U2.2 (SW6)
/Driver 2 and matrix/SW2_7: D95.1 (A), D96.1 (A), D97.1 (A), D98.1 (A), D201.1 (A), D203.1 (A), U2.9 (SW7)
/Driver 2 and matrix/SW2_8: D110.1 (A), D111.1 (A), D112.1 (A), D113.1 (A), D216.1 (A), D218.1 (A), U2.1 (SW8)
/Driver 2 and matrix/SW2_9: D125.1 (A), D126.1 (A), D127.1 (A), D128.1 (A), U2.10 (SW9)
/Driver 2 and matrix/SW2_10: D140.1 (A), D141.1 (A), D142.1 (A), D143.1 (A), U2.40 (SW10)
/Driver 2 and matrix/SW2_11: D155.1 (A), D156.1 (A), D157.1 (A), D158.1 (A), U2.11 (SW11)
I2C_SCL: U2.27 (SCL); also elsewhere on the board
I2C_SDA: U2.28 (SDA); also elsewhere on the board
LED_SDB: U2.26 (EN); also elsewhere on the board
unnamed: R33.1, U2.29 (ISET)
VSYS: C40.1, C41.1, C42.1, C43.1, C44.1, U2.5 (PVCC), U2.22 (VCC), U2.24 (AD1), U2.25 (AD0); also elsewhere on the board

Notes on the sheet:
DRIVER 2 (U2, 0x25)
60 MHPA0808RGBDT 0808 LEDS: A=Pin1, R=Pin2, G=Pin3, B=Pin4

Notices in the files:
hw/dense-square/s15-225/dense-square.kicad_pcb:
CERN-OHL-P-2.0
